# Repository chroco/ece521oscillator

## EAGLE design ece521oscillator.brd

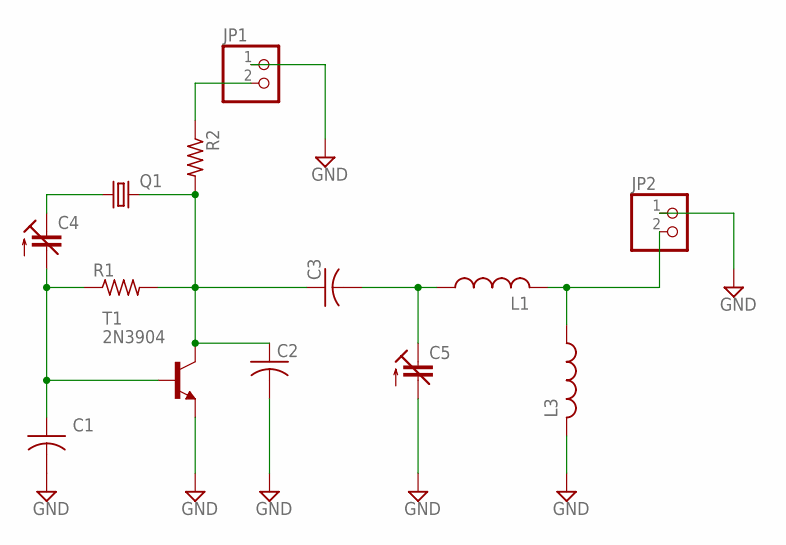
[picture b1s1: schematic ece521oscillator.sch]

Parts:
C1, C2, C3: C-US050-025X075; C050-025X075
C4, C5: C-TRIMM808; CTRIM808-BC
JP1, JP2: PINHD-1X2; 1X02
L1, L3: L-US0204/7; 0204/7
Q1: CRYSTALHC18U-V; HC18U-V
R1, R2: R-US_0204/7; 0204/7
T1: 2N3904; TO92

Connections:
GND: C1.2, C2.2, C5.2 (A), JP1.1, JP2.1, L3.2, T1.3 (E)
unnamed: C4.1 (E), Q1.1
unnamed: C1.1, C4.2 (A), R1.1, T1.2 (B)
unnamed: C2.1, C3.1, Q1.2, R1.2, R2.2, T1.1 (C)
unnamed: C3.2, C5.1 (E), L1.1
unnamed: JP2.2, L1.2, L3.1
unnamed: JP1.2, R2.1

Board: 2 copper layers, 13 parts (11 on the bottom side), 7 nets, no tracks yet.
